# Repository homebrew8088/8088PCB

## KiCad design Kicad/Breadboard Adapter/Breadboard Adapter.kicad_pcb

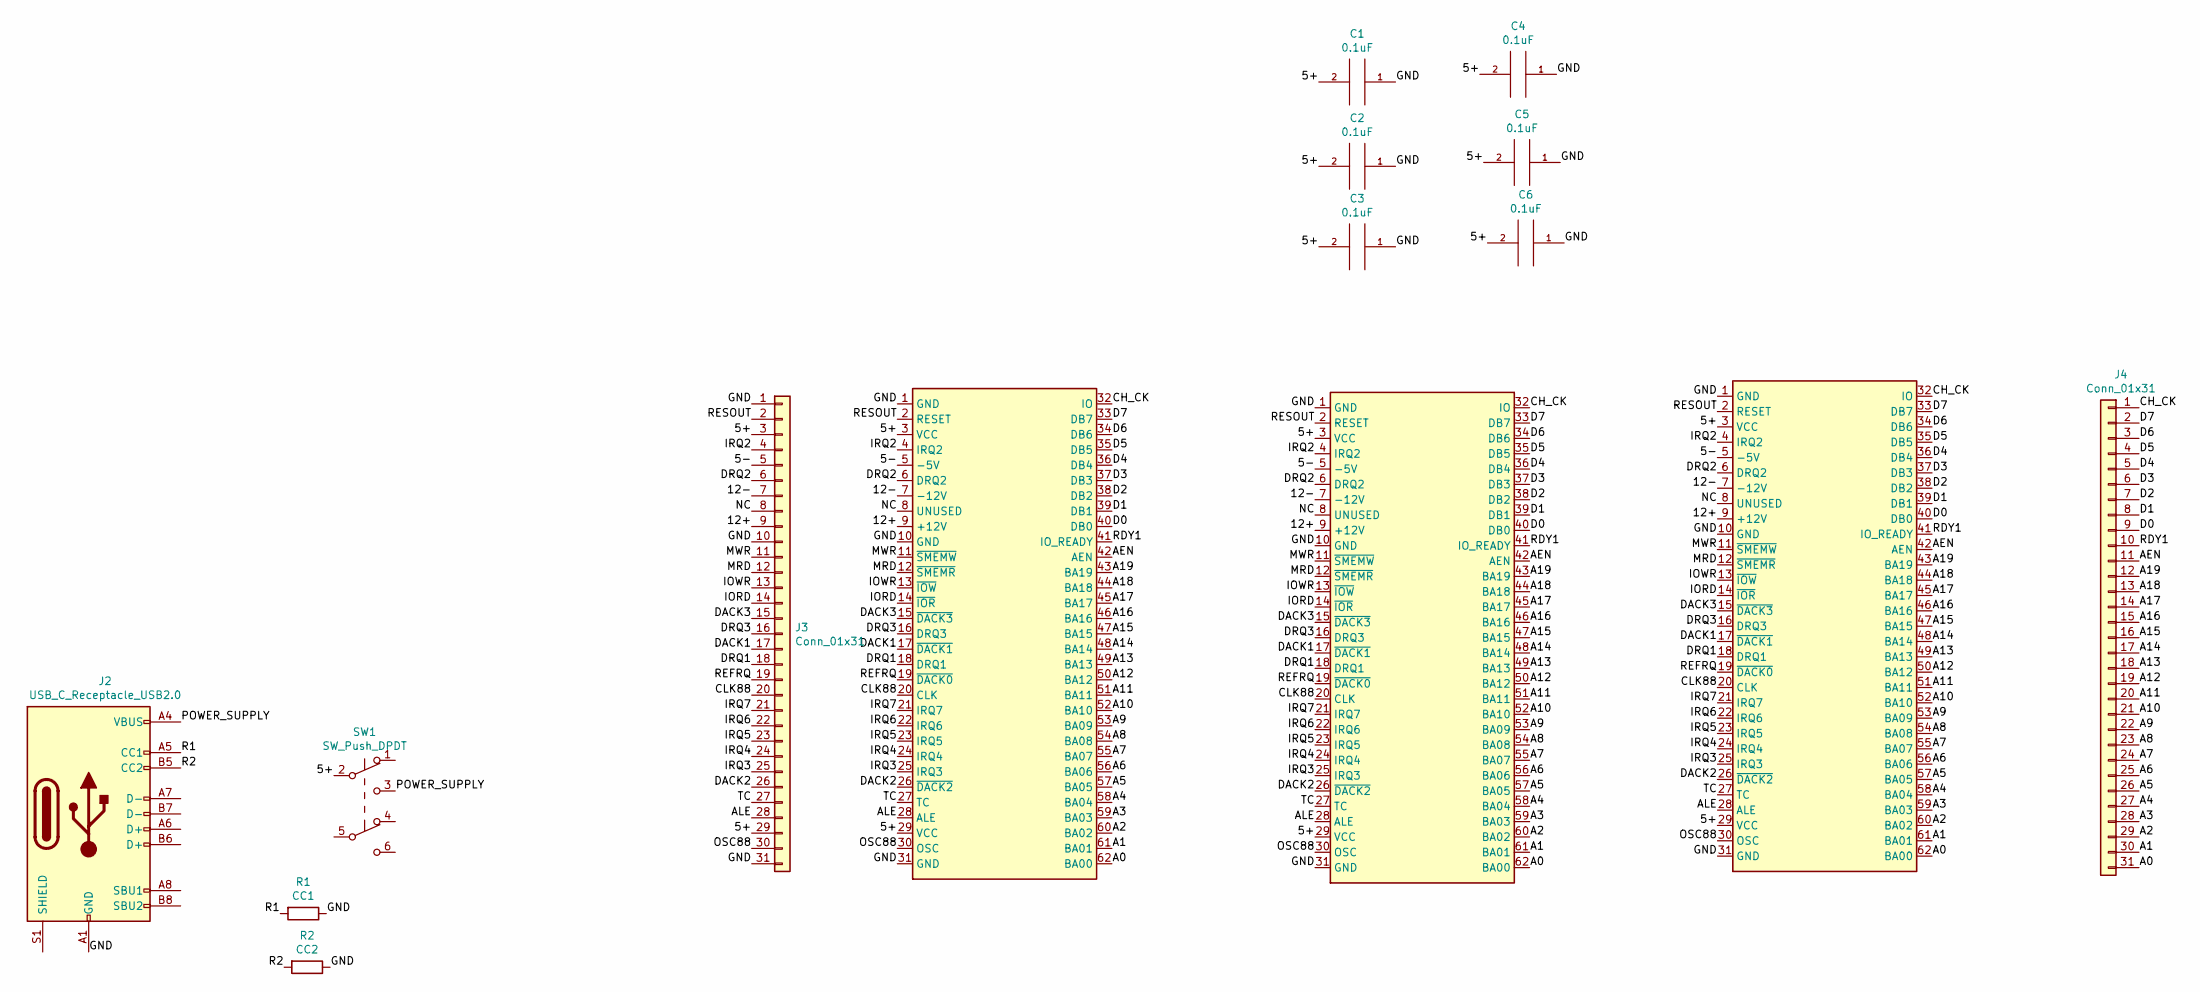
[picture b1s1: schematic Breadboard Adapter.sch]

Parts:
C1, C2, C3, C4, C5, C6: 0.1uF; C_Disc_D4.3mm_W1.9mm_P5.00mm
J1, J5, J9: Bus_ISA_8bit; 8-bit-ISA
J2: USB_C_Receptacle_USB2.0; USB_C_Receptacle_GCT_USB4085
J3, J4: Conn_01x31; PinHeader_1x31_P2.54mm_Vertical
R1: CC1; R_Axial_DIN0207_L6.3mm_D2.5mm_P10.16mm_Horizontal
R2: CC2; R_Axial_DIN0207_L6.3mm_D2.5mm_P10.16mm_Horizontal
SW1: SW_Push_DPDT; 6 PIN DTDP

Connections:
/5+: C1.2, C2.2, C3.2, C4.2, C5.2, C6.2, J1.3 (VCC), J1.29 (VCC), J3.3, J3.29, J5.3 (VCC), J5.29 (VCC), J9.3 (VCC), J9.29 (VCC), SW1.2 (B)
/5-: J1.5 (-5V), J3.5, J5.5 (-5V), J9.5 (-5V)
/12+: J1.9 (+12V), J3.9, J5.9 (+12V), J9.9 (+12V)
/12-: J1.7 (-12V), J3.7, J5.7 (-12V), J9.7 (-12V)
/A0: J1.62 (BA00), J4.31, J5.62 (BA00), J9.62 (BA00)
/A1: J1.61 (BA01), J4.30, J5.61 (BA01), J9.61 (BA01)
/A2: J1.60 (BA02), J4.29, J5.60 (BA02), J9.60 (BA02)
/A3: J1.59 (BA03), J4.28, J5.59 (BA03), J9.59 (BA03)
/A4: J1.58 (BA04), J4.27, J5.58 (BA04), J9.58 (BA04)
/A5: J1.57 (BA05), J4.26, J5.57 (BA05), J9.57 (BA05)
/A6: J1.56 (BA06), J4.25, J5.56 (BA06), J9.56 (BA06)
/A7: J1.55 (BA07), J4.24, J5.55 (BA07), J9.55 (BA07)
/A8: J1.54 (BA08), J4.23, J5.54 (BA08), J9.54 (BA08)
/A9: J1.53 (BA09), J4.22, J5.53 (BA09), J9.53 (BA09)
/A10: J1.52 (BA10), J4.21, J5.52 (BA10), J9.52 (BA10)
/A11: J1.51 (BA11), J4.20, J5.51 (BA11), J9.51 (BA11)
/A12: J1.50 (BA12), J4.19, J5.50 (BA12), J9.50 (BA12)
/A13: J1.49 (BA13), J4.18, J5.49 (BA13), J9.49 (BA13)
/A14: J1.48 (BA14), J4.17, J5.48 (BA14), J9.48 (BA14)
/A15: J1.47 (BA15), J4.16, J5.47 (BA15), J9.47 (BA15)
/A16: J1.46 (BA16), J4.15, J5.46 (BA16), J9.46 (BA16)
/A17: J1.45 (BA17), J4.14, J5.45 (BA17), J9.45 (BA17)
/A18: J1.44 (BA18), J4.13, J5.44 (BA18), J9.44 (BA18)
/A19: J1.43 (BA19), J4.12, J5.43 (BA19), J9.43 (BA19)
/AEN: J1.42 (AEN), J4.11, J5.42 (AEN), J9.42 (AEN)
/ALE: J1.28 (ALE), J3.28, J5.28 (ALE), J9.28 (ALE)
/CH_CK: J1.32 (IO), J4.1, J5.32 (IO), J9.32 (IO)
/CLK88: J1.20 (CLK), J3.20, J5.20 (CLK), J9.20 (CLK)
/D0: J1.40 (DB0), J4.9, J5.40 (DB0), J9.40 (DB0)
/D1: J1.39 (DB1), J4.8, J5.39 (DB1), J9.39 (DB1)
/D2: J1.38 (DB2), J4.7, J5.38 (DB2), J9.38 (DB2)
/D3: J1.37 (DB3), J4.6, J5.37 (DB3), J9.37 (DB3)
/D4: J1.36 (DB4), J4.5, J5.36 (DB4), J9.36 (DB4)
/D5: J1.35 (DB5), J4.4, J5.35 (DB5), J9.35 (DB5)
/D6: J1.34 (DB6), J4.3, J5.34 (DB6), J9.34 (DB6)
/D7: J1.33 (DB7), J4.2, J5.33 (DB7), J9.33 (DB7)
/DACK1: J1.17 (~DACK1), J3.17, J5.17 (~DACK1), J9.17 (~DACK1)
/DACK2: J1.26 (~DACK2), J3.26, J5.26 (~DACK2), J9.26 (~DACK2)
/DACK3: J1.15 (~DACK3), J3.15, J5.15 (~DACK3), J9.15 (~DACK3)
/DRQ1: J1.18 (DRQ1), J3.18, J5.18 (DRQ1), J9.18 (DRQ1)
/DRQ2: J1.6 (DRQ2), J3.6, J5.6 (DRQ2), J9.6 (DRQ2)
/DRQ3: J1.16 (DRQ3), J3.16, J5.16 (DRQ3), J9.16 (DRQ3)
/GND: C1.1, C2.1, C3.1, C4.1, C5.1, C6.1, J1.1 (GND), J1.10 (GND), J1.31 (GND), J2.A1 (GND), J2.A12 (GND), J2.B1 (GND), J2.B12 (GND), J3.1, J3.10, J3.31, J5.1 (GND), J5.10 (GND), J5.31 (GND), J9.1 (GND), J9.10 (GND), J9.31 (GND), R1.1, R2.1
/IORD: J1.14 (~IOR), J3.14, J5.14 (~IOR), J9.14 (~IOR)
/IOWR: J1.13 (~IOW), J3.13, J5.13 (~IOW), J9.13 (~IOW)
/IRQ2: J1.4 (IRQ2), J3.4, J5.4 (IRQ2), J9.4 (IRQ2)
/IRQ3: J1.25 (IRQ3), J3.25, J5.25 (IRQ3), J9.25 (IRQ3)
/IRQ4: J1.24 (IRQ4), J3.24, J5.24 (IRQ4), J9.24 (IRQ4)
/IRQ5: J1.23 (IRQ5), J3.23, J5.23 (IRQ5), J9.23 (IRQ5)
/IRQ6: J1.22 (IRQ6), J3.22, J5.22 (IRQ6), J9.22 (IRQ6)
/IRQ7: J1.21 (IRQ7), J3.21, J5.21 (IRQ7), J9.21 (IRQ7)
/MRD: J1.12 (~SMEMR), J3.12, J5.12 (~SMEMR), J9.12 (~SMEMR)
/MWR: J1.11 (~SMEMW), J3.11, J5.11 (~SMEMW), J9.11 (~SMEMW)
/NC: J1.8 (UNUSED), J3.8, J5.8 (UNUSED), J9.8 (UNUSED)
/OSC88: J1.30 (OSC), J3.30, J5.30 (OSC), J9.30 (OSC)
/POWER_SUPPLY: J2.A4 (VBUS), J2.A9 (VBUS), J2.B4 (VBUS), J2.B9 (VBUS), SW1.3 (C)
/R1: J2.A5 (CC1), R1.2
/R2: J2.B5 (CC2), R2.2
/RDY1: J1.41 (IO_READY), J4.10, J5.41 (IO_READY), J9.41 (IO_READY)
/REFRQ: J1.19 (~DACK0), J3.19, J5.19 (~DACK0), J9.19 (~DACK0)
/RESOUT: J1.2 (RESET), J3.2, J5.2 (RESET), J9.2 (RESET)
/TC: J1.27 (TC), J3.27, J5.27 (TC), J9.27 (TC)

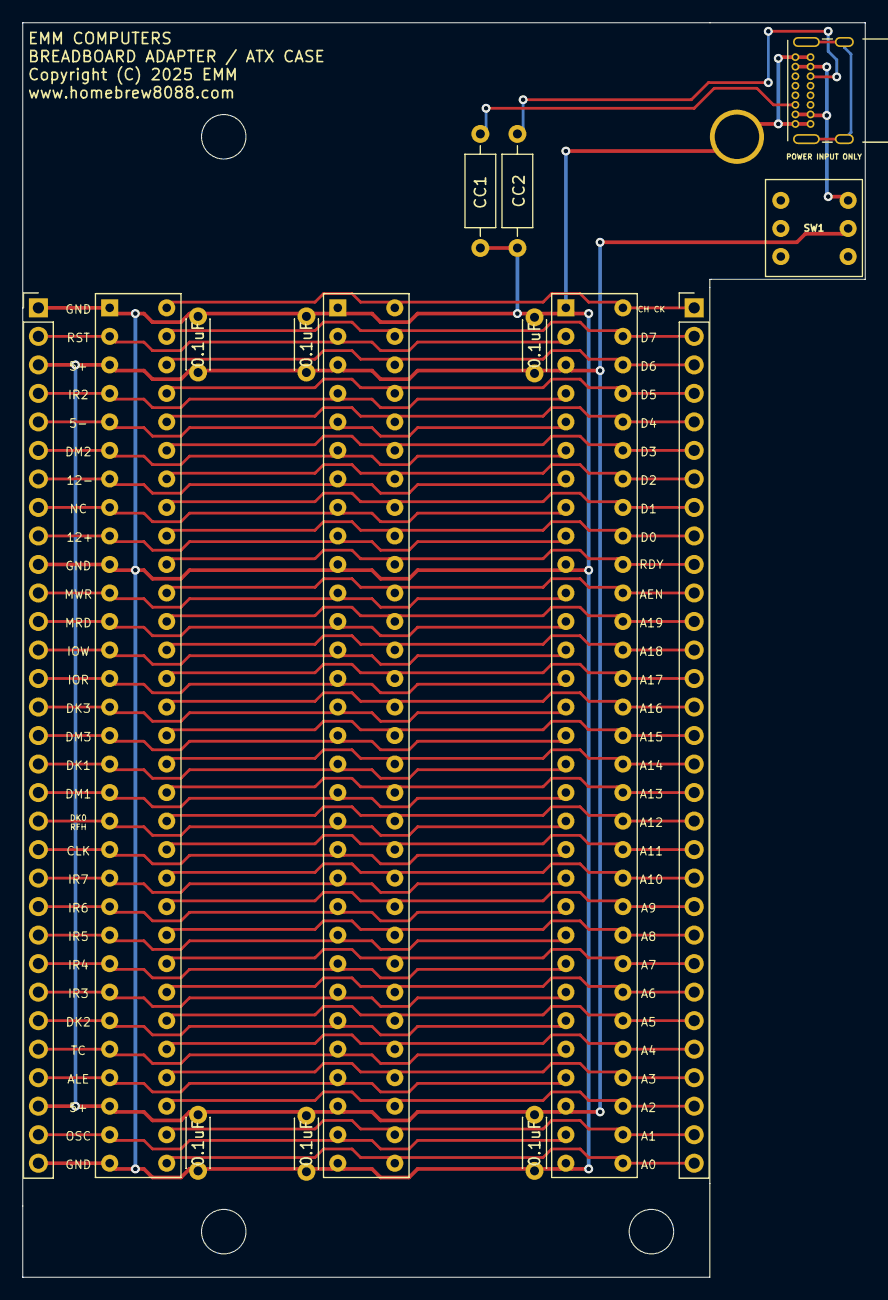
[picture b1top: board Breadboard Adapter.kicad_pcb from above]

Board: 2 copper layers, 75.1 x 111.8 mm, 15 parts (0 on the bottom side), 62 nets.

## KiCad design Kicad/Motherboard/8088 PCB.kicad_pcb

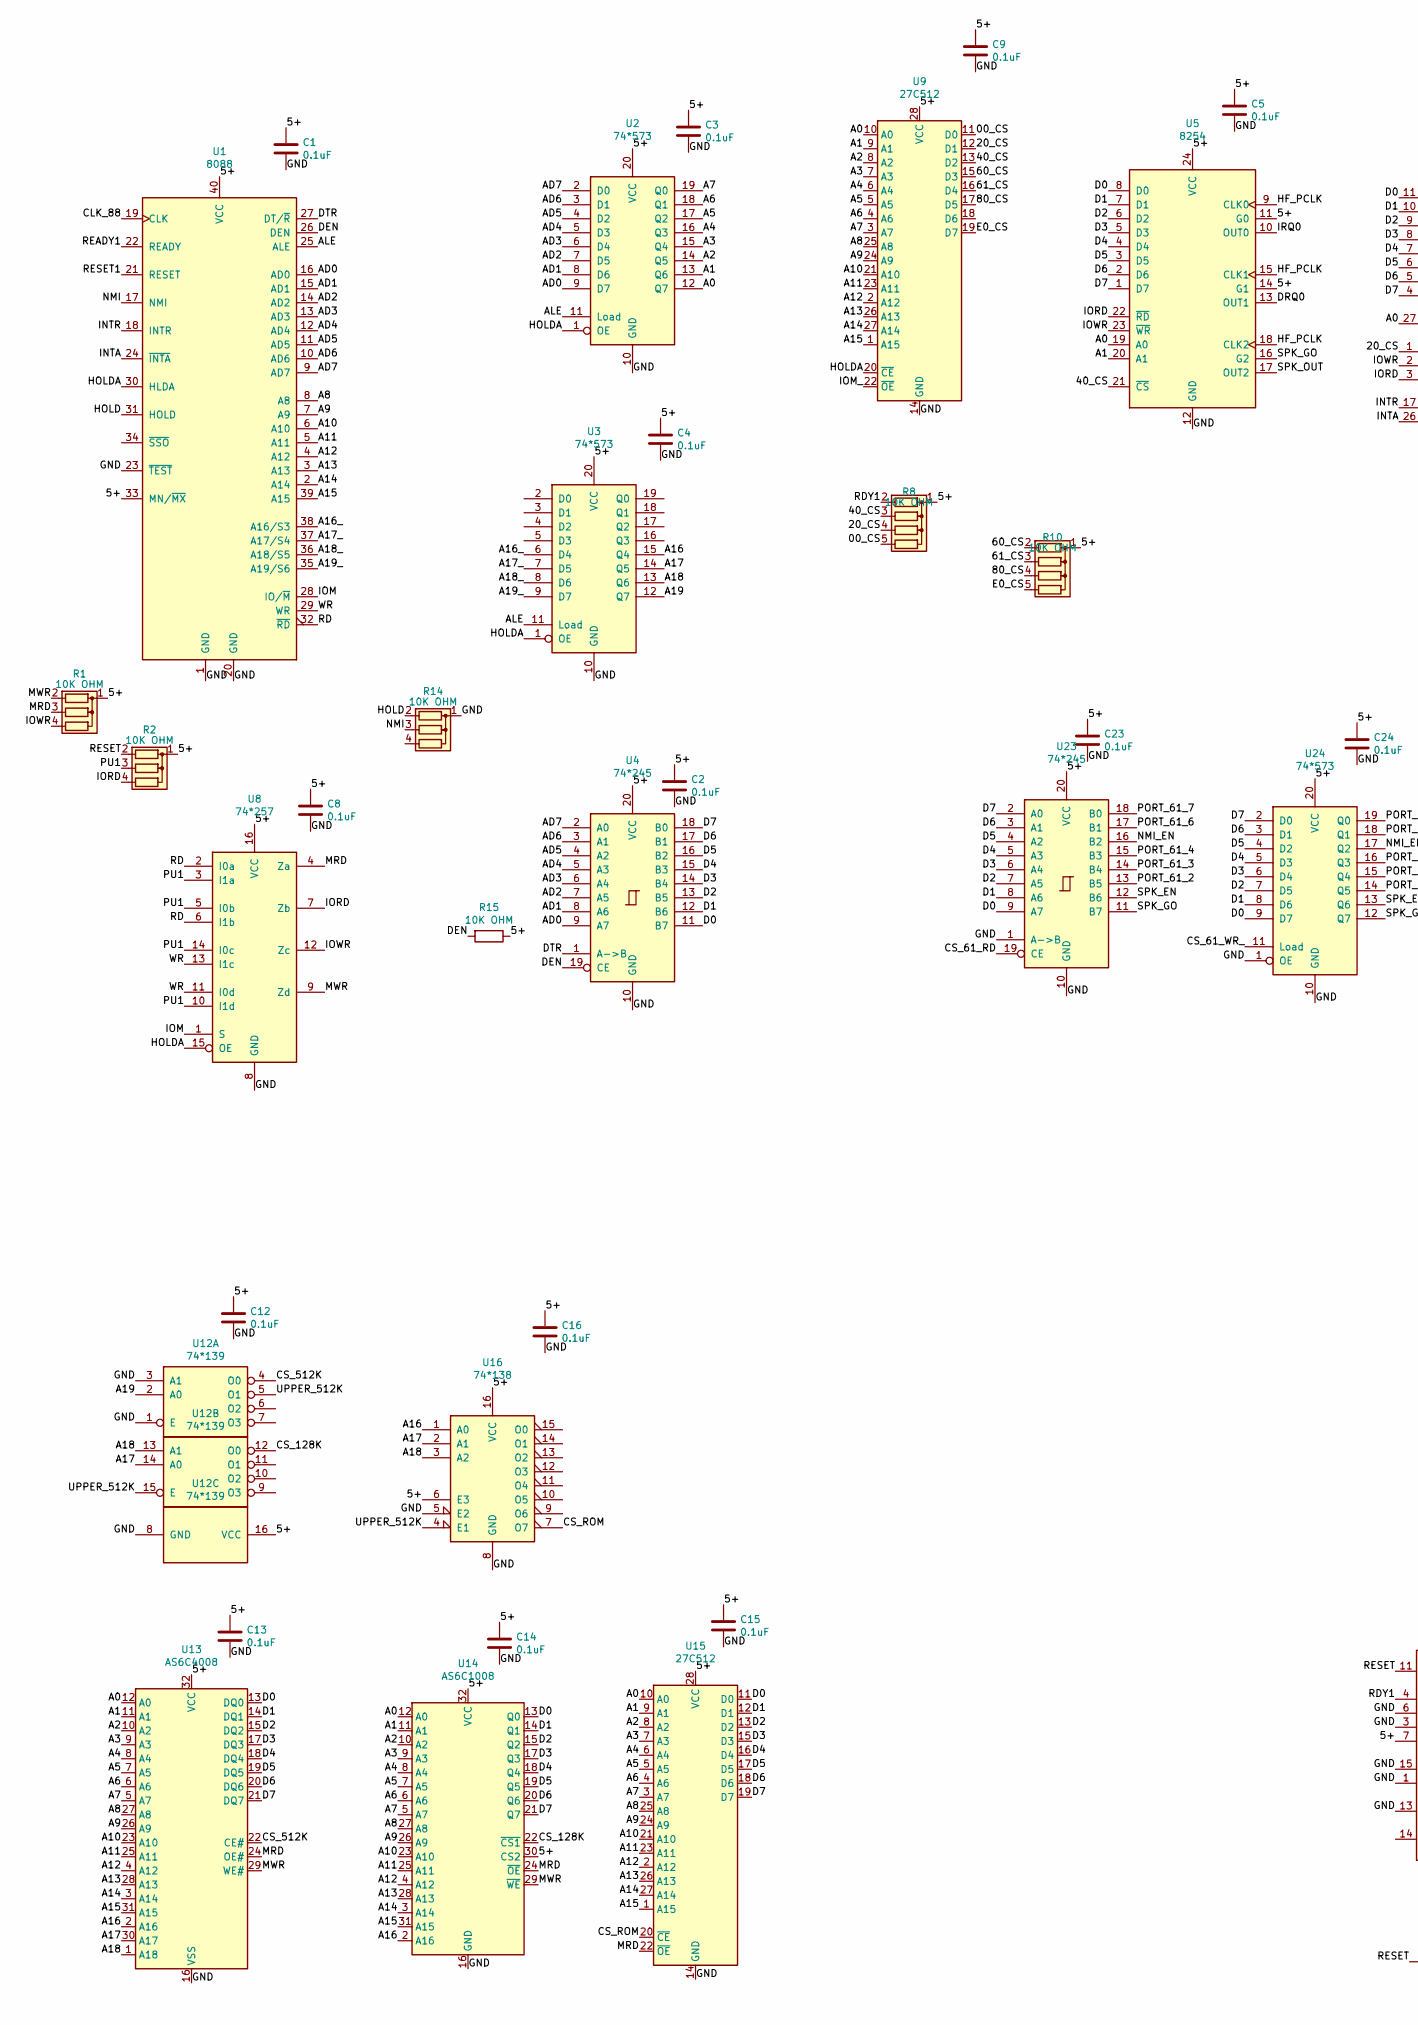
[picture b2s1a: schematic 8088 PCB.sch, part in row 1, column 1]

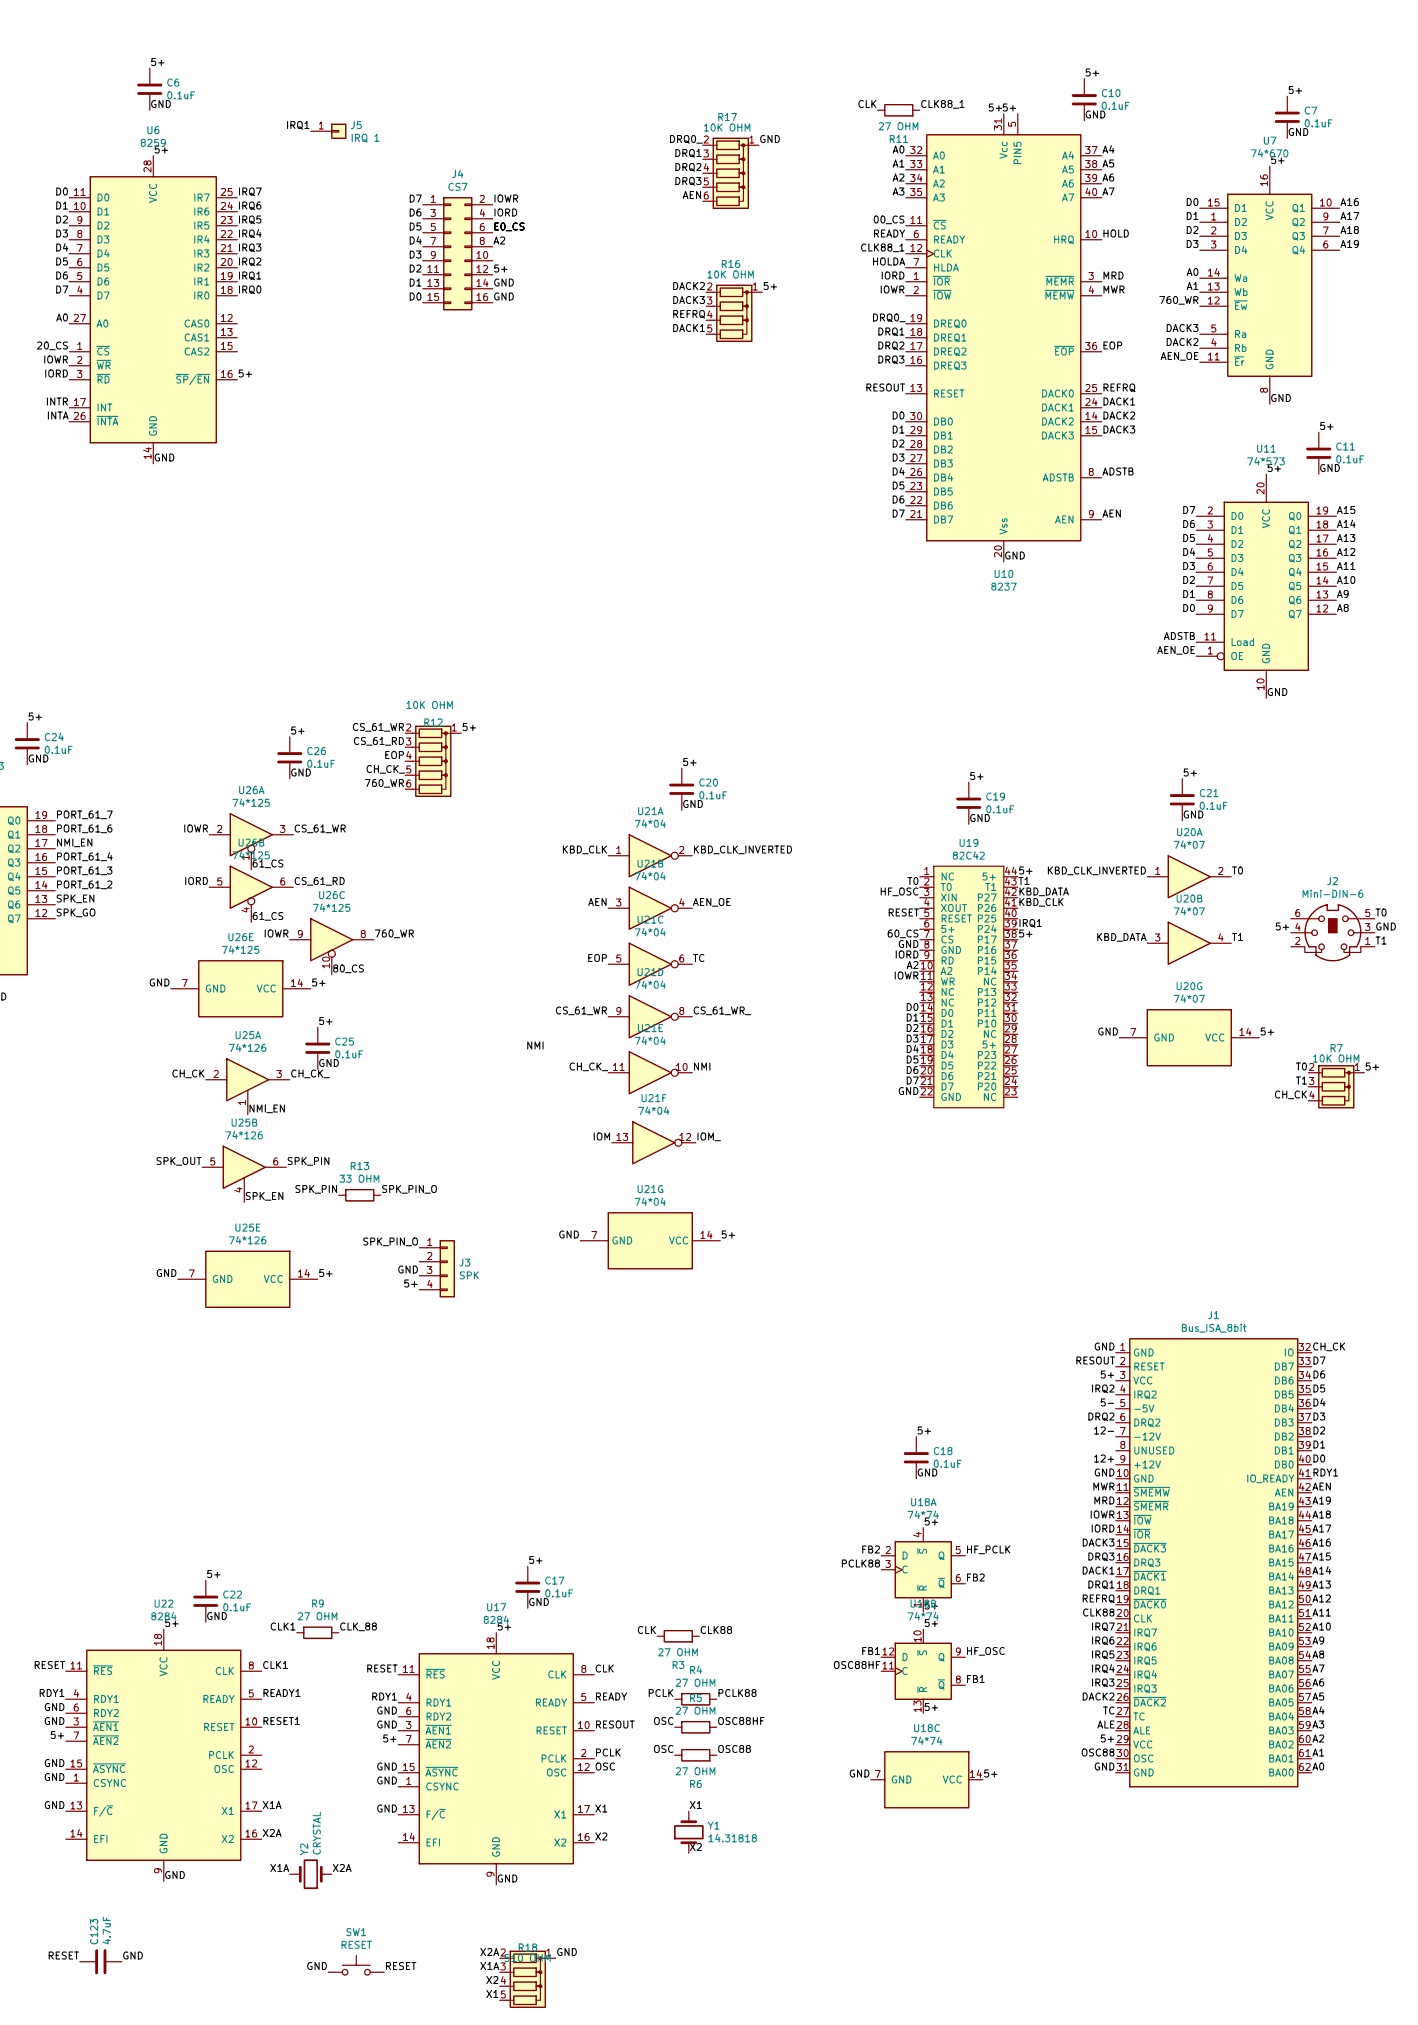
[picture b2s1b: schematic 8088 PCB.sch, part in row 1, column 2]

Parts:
C1, C2, C3, C4, C5, C6, C7, C8, C9, C10, C11, C12, C13, C14, C15, C16, C17, C18, C19, C20, C21, C22, C23, C24, C25, C26: 0.1uF; C_Disc_D4.3mm_W1.9mm_P5.00mm
C123: 4.7uF; CP_Radial_D4.0mm_P1.50mm
J1: Bus_ISA_8bit; BUS_8_BIT
J2: Mini-DIN-6; 6_PIN_DIN
J3: SPK; PinHeader_1x04_P2.54mm_Vertical
J4: CS7; PinHeader_2x08_P2.54mm_Vertical
J5: IRQ 1; PinHeader_1x01_P2.54mm_Vertical
R1, R2, R7, R14: 10K OHM; R_Array_SIP4
R3, R4, R5, R6, R9, R11: 27 OHM; R_Axial_DIN0207_L6.3mm_D2.5mm_P10.16mm_Horizontal
R8, R10, R16: 10K OHM; R_Array_SIP5
R12, R17: 10K OHM; R_Array_SIP6
R13: 33 OHM; R_Axial_DIN0207_L6.3mm_D2.5mm_P10.16mm_Horizontal
R15: 10K OHM; R_Axial_DIN0207_L6.3mm_D2.5mm_P10.16mm_Horizontal
R18: 510 OHM; R_Array_SIP5
SW1: RESET; SW_PUSH_6mm
U1: 8088; DIP-40_W15.24mm
U2, U3, U11, U24: 74*573; DIP-20_W7.62mm
U4, U23: 74*245; DIP-20_W7.62mm
U5: 8254; DIP-24_W15.24mm
U6: 8259; DIP-28_W15.24mm
U7: 74*670; DIP-16_W7.62mm
U8: 74*257; DIP-16_W7.62mm
U9, U15: 27C512; DIP-28_W15.24mm
U10: 8237; DIP-40_W15.24mm
U12: 74*139; DIP-16_W7.62mm
U13: AS6C4008; DIP-32_W15.24mm
U14: AS6C1008; DIP-32_W15.24mm
U16: 74*138; DIP-16_W7.62mm
U17, U22: 8284; DIP-18_W7.62mm
U18: 74*74; DIP-14_W7.62mm
U19: 82C42; PLCC-44_THT-Socket
U20: 74*07; DIP-14_W7.62mm
U21: 74*04; DIP-14_W7.62mm
U25: 74*126; DIP-14_W7.62mm
U26: 74*125; DIP-14_W7.62mm
Y1: 14.31818; Crystal_HC18-U_Vertical
Y2: CRYSTAL; Crystal_HC18-U_Vertical

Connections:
/00_CS: R8.5 (R4), U9.11 (D0), U10.11 (~CS~)
/5+: C1.1, C2.1, C3.1, C4.1, C5.1, C6.1, C7.1, C8.1, C9.1, C10.1, C11.1, C12.1, C13.1, C14.1, C15.1, C16.1, C17.1, C18.1, C19.1, C20.1, C21.1, C22.1, C23.1, C24.1, C25.1, C26.1, J1.3 (VCC), J1.29 (VCC), J2.4, J3.4, J4.12, R1.1 (common), R2.1 (common), R7.1 (common), R8.1 (common), R10.1 (common), R12.1 (common), R15.1, R16.1 (common), U1.33 (MN/~MX~), U1.40 (VCC), U2.20 (VCC), U3.20 (VCC), U4.20 (VCC), U5.11 (G0), U5.14 (G1), U5.24 (VCC), U6.16 (~SP~/~EN~), U6.28 (VCC), U7.16 (VCC), U8.16 (VCC), U9.28 (VCC), U10.5 (PIN5), U10.31 (Vcc), U11.20 (VCC), U12.16 (VCC), U13.32 (VCC), U14.30 (CS2), U14.32 (VCC), U15.28 (VCC), U16.6 (E3), U16.16 (VCC), U17.7 (~AEN2~), U17.18 (VCC), U18.1 (~R), U18.4 (~S), U18.10 (~S), U18.13 (~R), U18.14 (VCC), U19.38 (P17), U19.44 (5+), U20.14 (VCC), U21.14 (VCC), U22.7 (~AEN2~), U22.18 (VCC), U23.20 (VCC), U24.20 (VCC), U25.14 (VCC), U26.14 (VCC)
/5-: J1.5 (-5V)
/12+: J1.9 (+12V)
/12-: J1.7 (-12V)
/20_CS: R8.4 (R3), U6.1 (~CS~), U9.12 (D1)
/40_CS: R8.3 (R2), U5.21 (~CS~), U9.13 (D2)
/60_CS: R10.2 (R1), U9.15 (D3), U19.7 (CS)
/61_CS: R10.3 (R2), U9.16 (D4), U26.1, U26.4
/80_CS: R10.4 (R3), U9.17 (D5), U26.10
/760_WR: R12.6 (R5), U7.12 (~Ew), U26.8
/A0: J1.62 (BA00), U2.12 (Q7), U5.19 (A0), U6.27 (A0), U7.14 (Wa), U9.10 (A0), U10.32 (A0), U13.12 (A0), U14.12 (A0), U15.10 (A0)
/A1: J1.61 (BA01), U2.13 (Q6), U5.20 (A1), U7.13 (Wb), U9.9 (A1), U10.33 (A1), U13.11 (A1), U14.11 (A1), U15.9 (A1)
/A2: J1.60 (BA02), J4.8, U2.14 (Q5), U9.8 (A2), U10.34 (A2), U13.10 (A2), U14.10 (A2), U15.8 (A2), U19.10 (A2)
/A3: J1.59 (BA03), U2.15 (Q4), U9.7 (A3), U10.35 (A3), U13.9 (A3), U14.9 (A3), U15.7 (A3)
/A4: J1.58 (BA04), U2.16 (Q3), U9.6 (A4), U10.37 (A4), U13.8 (A4), U14.8 (A4), U15.6 (A4)
/A5: J1.57 (BA05), U2.17 (Q2), U9.5 (A5), U10.38 (A5), U13.7 (A5), U14.7 (A5), U15.5 (A5)
/A6: J1.56 (BA06), U2.18 (Q1), U9.4 (A6), U10.39 (A6), U13.6 (A6), U14.6 (A6), U15.4 (A6)
/A7: J1.55 (BA07), U2.19 (Q0), U9.3 (A7), U10.40 (A7), U13.5 (A7), U14.5 (A7), U15.3 (A7)
/A8: J1.54 (BA08), U1.8 (A8), U9.25 (A8), U11.12 (Q7), U13.27 (A8), U14.27 (A8), U15.25 (A8)
/A9: J1.53 (BA09), U1.7 (A9), U9.24 (A9), U11.13 (Q6), U13.26 (A9), U14.26 (A9), U15.24 (A9)
/A10: J1.52 (BA10), U1.6 (A10), U9.21 (A10), U11.14 (Q5), U13.23 (A10), U14.23 (A10), U15.21 (A10)
/A11: J1.51 (BA11), U1.5 (A11), U9.23 (A11), U11.15 (Q4), U13.25 (A11), U14.25 (A11), U15.23 (A11)
/A12: J1.50 (BA12), U1.4 (A12), U9.2 (A12), U11.16 (Q3), U13.4 (A12), U14.4 (A12), U15.2 (A12)
/A13: J1.49 (BA13), U1.3 (A13), U9.26 (A13), U11.17 (Q2), U13.28 (A13), U14.28 (A13), U15.26 (A13)
/A14: J1.48 (BA14), U1.2 (A14), U9.27 (A14), U11.18 (Q1), U13.3 (A14), U14.3 (A14), U15.27 (A14)
/A15: J1.47 (BA15), U1.39 (A15), U9.1 (A15), U11.19 (Q0), U13.31 (A15), U14.31 (A15), U15.1 (A15)
/A16: J1.46 (BA16), U3.15 (Q4), U7.10 (Q1), U13.2 (A16), U14.2 (A16), U16.1 (A0)
/A16_: U1.38 (A16/S3), U3.6 (D4)
/A17: J1.45 (BA17), U3.14 (Q5), U7.9 (Q2), U12.14 (A0), U13.30 (A17), U16.2 (A1)
/A17_: U1.37 (A17/S4), U3.7 (D5)
/A18: J1.44 (BA18), U3.13 (Q6), U7.7 (Q3), U12.13 (A1), U13.1 (A18), U16.3 (A2)
/A18_: U1.36 (A18/S5), U3.8 (D6)
/A19: J1.43 (BA19), U3.12 (Q7), U7.6 (Q4), U12.2 (A0)
/A19_: U1.35 (A19/S6), U3.9 (D7)
/AD0: U1.16 (AD0), U2.9 (D7), U4.9 (A7)
/AD1: U1.15 (AD1), U2.8 (D6), U4.8 (A6)
/AD2: U1.14 (AD2), U2.7 (D5), U4.7 (A5)
/AD3: U1.13 (AD3), U2.6 (D4), U4.6 (A4)
/AD4: U1.12 (AD4), U2.5 (D3), U4.5 (A3)
/AD5: U1.11 (AD5), U2.4 (D2), U4.4 (A2)
/AD6: U1.10 (AD6), U2.3 (D1), U4.3 (A1)
/AD7: U1.9 (AD7), U2.2 (D0), U4.2 (A0)
/ADSTB: U10.8 (ADSTB), U11.11 (Load)
/AEN: J1.42 (AEN), R17.6 (R5), U10.9 (AEN), U21.3
/AEN_OE: U7.11 (~Er), U11.1 (OE), U21.4
/ALE: J1.28 (ALE), U1.25 (ALE), U2.11 (Load), U3.11 (Load)
/CH_CK: J1.32 (IO), R7.4 (R3), U25.2
/CH_CK_: R12.5 (R4), U21.11, U25.3
/CLK: R3.1, R11.1, U17.8 (CLK)
/CLK1: R9.2, U22.8 (CLK)
/CLK88: J1.20 (CLK), R3.2
/CLK88_1: R11.2, U10.12 (CLK)
/CLK_88: R9.1, U1.19 (CLK)
/CS_61_RD: R12.3 (R2), U23.19 (CE), U26.6
/CS_61_WR: R12.2 (R1), U21.9, U26.3
/CS_61_WR_: U21.8, U24.11 (Load)
/CS_128K: U12.12 (O0), U14.22 (~CS1)
/CS_512K: U12.4 (O0), U13.22 (CE#)
/CS_ROM: U15.20 (~CE), U16.7 (O7)
/D0: J1.40 (DB0), J4.15, U4.11 (B7), U5.8 (D0), U6.11 (D0), U7.15 (D1), U10.30 (DB0), U11.9 (D7), U13.13 (DQ0), U14.13 (Q0), U15.11 (D0), U19.14 (D0), U23.9 (A7), U24.9 (D7)
/D1: J1.39 (DB1), J4.13, U4.12 (B6), U5.7 (D1), U6.10 (D1), U7.1 (D2), U10.29 (DB1), U11.8 (D6), U13.14 (DQ1), U14.14 (Q1), U15.12 (D1), U19.15 (D1), U23.8 (A6), U24.8 (D6)
/D2: J1.38 (DB2), J4.11, U4.13 (B5), U5.6 (D2), U6.9 (D2), U7.2 (D3), U10.28 (DB2), U11.7 (D5), U13.15 (DQ2), U14.15 (Q2), U15.13 (D2), U19.16 (D2), U23.7 (A5), U24.7 (D5)
/D3: J1.37 (DB3), J4.9, U4.14 (B4), U5.5 (D3), U6.8 (D3), U7.3 (D4), U10.27 (DB3), U11.6 (D4), U13.17 (DQ3), U14.17 (Q3), U15.15 (D3), U19.17 (D3), U23.6 (A4), U24.6 (D4)
/D4: J1.36 (DB4), J4.7, U4.15 (B3), U5.4 (D4), U6.7 (D4), U10.26 (DB4), U11.5 (D3), U13.18 (DQ4), U14.18 (Q4), U15.16 (D4), U19.18 (D4), U23.5 (A3), U24.5 (D3)
/D5: J1.35 (DB5), J4.5, U4.16 (B2), U5.3 (D5), U6.6 (D5), U10.23 (DB5), U11.4 (D2), U13.19 (DQ5), U14.19 (Q5), U15.17 (D5), U19.19 (D5), U23.4 (A2), U24.4 (D2)
/D6: J1.34 (DB6), J4.3, U4.17 (B1), U5.2 (D6), U6.5 (D6), U10.22 (DB6), U11.3 (D1), U13.20 (DQ6), U14.20 (Q6), U15.18 (D6), U19.20 (D6), U23.3 (A1), U24.3 (D1)
/D7: J1.33 (DB7), J4.1, U4.18 (B0), U5.1 (D7), U6.4 (D7), U10.21 (DB7), U11.2 (D0), U13.21 (DQ7), U14.21 (Q7), U15.19 (D7), U19.21 (D7), U23.2 (A0), U24.2 (D0)
/DACK1: J1.17 (~DACK1), R16.5 (R4), U10.24 (DACK1)
/DACK2: J1.26 (~DACK2), R16.2 (R1), U7.4 (Rb), U10.14 (DACK2)
/DACK3: J1.15 (~DACK3), R16.3 (R2), U7.5 (Ra), U10.15 (DACK3)
/DEN: R15.2, U1.26 (DEN), U4.19 (CE)
/DRQ0: U5.13 (OUT1)
/DRQ0_: R17.2 (R1), U10.19 (DREQ0)
/DRQ1: J1.18 (DRQ1), R17.3 (R2), U10.18 (DREQ1)
/DRQ2: J1.6 (DRQ2), R17.4 (R3), U10.17 (DREQ2)
/DRQ3: J1.16 (DRQ3), R17.5 (R4), U10.16 (DREQ3)
/DTR: U1.27 (DT/~R~), U4.1 (A->B)
/E0_CS: J4.6, R10.5 (R4), U9.19 (D7)
/EOP: R12.4 (R3), U10.36 (~EOP~), U21.5
/FB1: U18.8 (~Q), U18.12 (D)
/FB2: U18.2 (D), U18.6 (~Q)
/GND: C1.2, C2.2, C3.2, C4.2, C5.2, C6.2, C7.2, C8.2, C9.2, C10.2, C11.2, C12.2, C13.2, C14.2, C15.2, C16.2, C17.2, C18.2, C19.2, C20.2, C21.2, C22.2, C23.2, C24.2, C25.2, C26.2, C123.2, J1.1 (GND), J1.10 (GND), J1.31 (GND), J2.3, J3.3, J4.14, J4.16, R14.1 (common), R17.1 (common), R18.1 (common), SW1.1, U1.1 (GND), U1.20 (GND), U1.23 (~TEST~), U2.10 (GND), U3.10 (GND), U4.10 (GND), U5.12 (GND), U6.14 (GND), U7.8 (GND), U8.8 (GND), U9.14 (GND), U10.20 (Vss), U11.10 (GND), U12.1 (E), U12.3 (A1), U12.8 (GND), U13.16 (VSS), U14.16 (GND), U15.14 (GND), U16.5 (E2), U16.8 (GND), U17.1 (CSYNC), U17.3 (~AEN1~), U17.6 (RDY2), U17.9 (GND), U17.13 (F/~C~), U17.15 (~ASYNC~), U18.7 (GND), U19.8 (GND), U19.22 (GND), U20.7 (GND), U21.7 (GND), U22.1 (CSYNC), U22.3 (~AEN1~), U22.6 (RDY2), U22.9 (GND), U22.13 (F/~C~), U22.15 (~ASYNC~), U23.1 (A->B), U23.10 (GND), U24.1 (OE), U24.10 (GND), U25.7 (GND), U26.7 (GND); also elsewhere on the board
/HF_OSC: U18.9 (Q), U19.3 (XIN)
/HF_PCLK: U5.9 (CLK0), U5.15 (CLK1), U5.18 (CLK2), U18.5 (Q)
/HOLD: R14.2 (R1), U1.31 (HOLD), U10.10 (HRQ)
/HOLDA: U1.30 (HLDA), U2.1 (OE), U3.1 (OE), U8.15 (OE), U9.20 (~CE), U10.7 (HLDA)
/INTA: U1.24 (~INTA~), U6.26 (~INTA~)
/INTR: U1.18 (INTR), U6.17 (INT)
/IOM: U1.28 (IO/~M~), U8.1 (S), U21.13
/IOM_: U9.22 (~OE), U21.12
/IORD: J1.14 (~IOR), J4.4, R2.4 (R3), U5.22 (~RD~), U6.3 (~RD~), U8.7 (Zb), U10.1 (~IOR~), U19.9 (RD), U26.5
/IOWR: J1.13 (~IOW), J4.2, R1.4 (R3), U5.23 (~WR~), U6.2 (~WR~), U8.12 (Zc), U10.2 (~IOW~), U19.11 (WR), U26.2, U26.9
/IRQ0: U5.10 (OUT0), U6.18 (IR0)
/IRQ1: J5.1, U6.19 (IR1), U19.39 (P24)
/IRQ2: J1.4 (IRQ2), U6.20 (IR2)
/IRQ3: J1.25 (IRQ3), U6.21 (IR3)
/IRQ4: J1.24 (IRQ4), U6.22 (IR4)
/IRQ5: J1.23 (IRQ5), U6.23 (IR5)
/IRQ6: J1.22 (IRQ6), U6.24 (IR6)
/IRQ7: J1.21 (IRQ7), U6.25 (IR7)
/KBD_CLK: U19.41 (P26), U21.1
/KBD_CLK_INVERTED: U20.1, U21.2
/KBD_DATA: U19.42 (P27), U20.3
/MRD: J1.12 (~SMEMR), R1.3 (R2), U8.4 (Za), U10.3 (~MEMR~), U13.24 (OE#), U14.24 (~OE), U15.22 (~OE)
/MWR: J1.11 (~SMEMW), R1.2 (R1), U8.9 (Zd), U10.4 (~MEMW~), U13.29 (WE#), U14.29 (~WE)
/NMI: R14.3 (R2), U1.17 (NMI), U21.10
/NMI_EN: U23.16 (B2), U24.17 (Q2), U25.1
/OSC: R5.2, R6.1, U17.12 (OSC)
/OSC88: J1.30 (OSC), R6.2
/OSC88HF: R5.1, U18.11 (C)
/PCLK: R4.2, U17.2 (PCLK)
/PCLK88: R4.1, U18.3 (C)
/PORT_61_2: U23.13 (B5), U24.14 (Q5)
/PORT_61_3: U23.14 (B4), U24.15 (Q4)
/PORT_61_4: U23.15 (B3), U24.16 (Q3)
/PORT_61_6: U23.17 (B1), U24.18 (Q1)
/PORT_61_7: U23.18 (B0), U24.19 (Q0)
/PU1: R2.3 (R2), U8.3 (I1a), U8.5 (I0b), U8.10 (I1d), U8.14 (I0c)
/RD: U1.32 (~RD~), U8.2 (I0a), U8.6 (I1b)
/RDY1: J1.41 (IO_READY), R8.2 (R1), U17.4 (RDY1), U22.4 (RDY1)
/READY: U10.6 (READY), U17.5 (READY)
/READY1: U1.22 (READY), U22.5 (READY)
/REFRQ: J1.19 (~DACK0), R16.4 (R3), U10.25 (DACK0)
/RESET: C123.1, R2.2 (R1), SW1.2, U17.11 (~RES~), U19.5 (RESET), U22.11 (~RES~)
/RESET1: U1.21 (RESET), U22.10 (RESET)
/RESOUT: J1.2 (RESET), U10.13 (RESET), U17.10 (RESET)
/SPK_EN: U23.12 (B6), U24.13 (Q6), U25.4
/SPK_GO: U5.16 (G2), U23.11 (B7), U24.12 (Q7)
/SPK_OUT: U5.17 (OUT2), U25.5
/SPK_PIN: R13.2, U25.6
/SPK_PIN_O: J3.1, R13.1
/T0: J2.5, R7.2 (R1), U19.2 (T0), U20.2
/T1: J2.1, R7.3 (R2), U19.43 (T1), U20.4
/TC: J1.27 (TC), U21.6
/UPPER_512K: U12.5 (O1), U12.15 (E), U16.4 (E1)
/WR: U1.29 (WR), U8.11 (I0d), U8.13 (I1c)
/X1: R18.5 (R4), U17.17 (X1), Y1.2
/X1A: R18.3 (R2), U22.17 (X1), Y2.2
/X2: R18.4 (R3), U17.16 (X2), Y1.1
/X2A: R18.2 (R1), U22.16 (X2), Y2.1

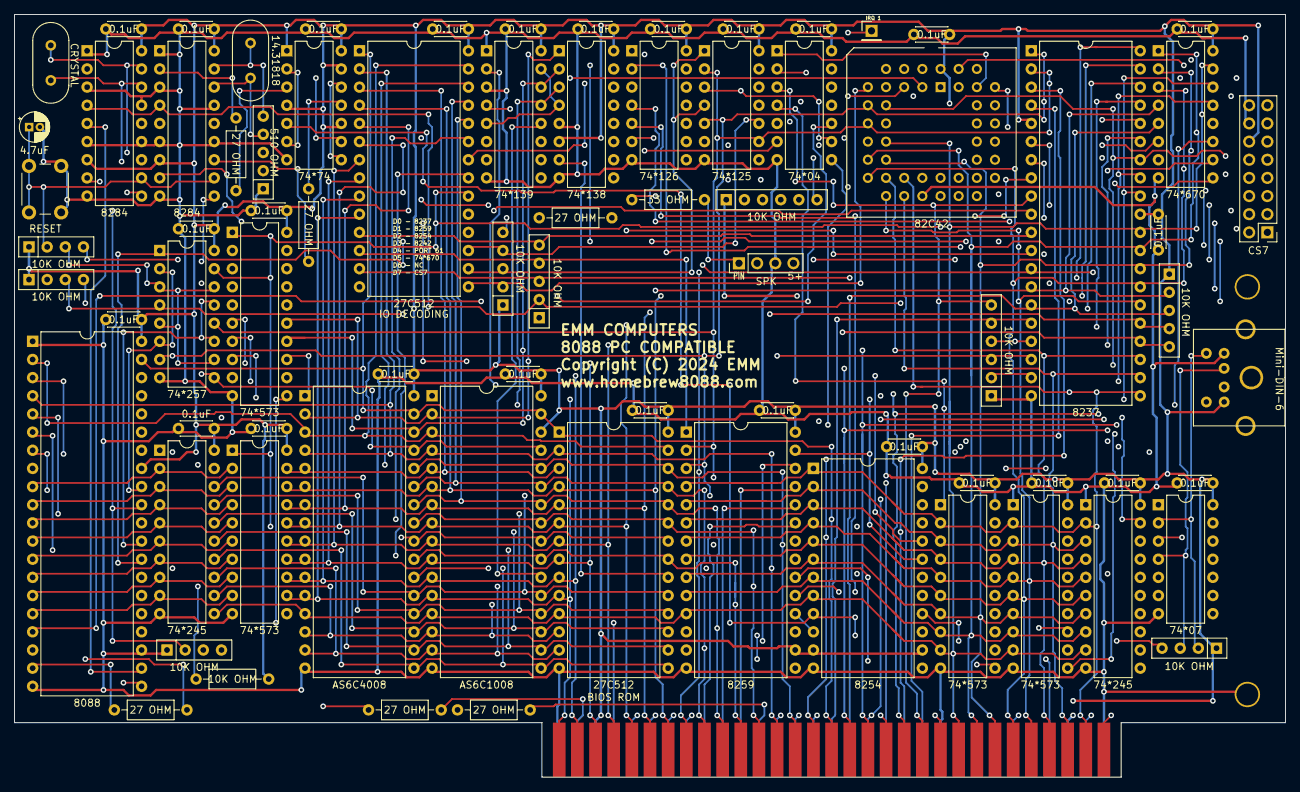
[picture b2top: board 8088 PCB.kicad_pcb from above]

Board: 4 copper layers, 177.8 x 106.7 mm, 81 parts (0 on the bottom side), 137 nets.

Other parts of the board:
R: L; Large_Via
R#2: L; Large_Via

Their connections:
/GND: R#2.1; also elsewhere on the board

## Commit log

2024-05-01 Create
2024-05-03 Added CH376 conn
2024-05-06 update for production
2024-05-17 17 May 24 build
2024-05-27 Update IRQ 1 pin
2024-05-28 update adapter
2025-01-31 Up dated Breadboard adpater

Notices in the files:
Kicad/Breadboard Adapter/Breadboard Adapter.kicad_pcb:
Copyright (C) 2025 EMM
Kicad/Motherboard/8088 PCB.kicad_pcb:
Copyright (C) 2024 EMM
